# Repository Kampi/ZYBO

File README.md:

# ZYBO

## Table of Contents

- [ZYBO](#zybo)
  - [Table of Contents](#table-of-contents)
  - [About](#about)
  - [Examples](#examples)
  - [Projects](#projects)
  - [Pmod](#pmod)
  - [Maintainer](#maintainer)

## About

This repository contains several VHDL/C/Linux examples for [ZYNQ](https://www.xilinx.com/products/silicon-devices/soc/zynq-7000.html) devices from Xilinx which are designed for my [ZYBO](https://store.digilentinc.com/zybo-zynq-7000-arm-fpga-soc-trainer-board/).

Please visit my [blog](https://www.kampis-elektroecke.de/) when you need more information about the examples or about the projects.

## Examples

This directory contains the following examples from my ZYNQ tutorial:

| **Example** | **Description** |
|---|---|
| ProcessingSystem | Simple design to learn how to use the programmable logic and the [Processing System](https://www.xilinx.com/support/documentation/ip_documentation/processing_system7/v5_5/pg082-processing-system7.pdf) to read and write I/O by using the [AXI GPIO](https://www.xilinx.com/support/documentation/ip_documentation/axi_gpio/v2_0/pg144-axi-gpio.pdf). |
| Interrupts | Basic interrupt example to understand the ARM and programmable logic interrupt system. |
| XADC | Learn and understand how to use the integrated [XADC](https://www.xilinx.com/support/documentation/user_guides/ug480_7Series_XADC.pdf) to sample analog values. |
| FIFO | Small example how to use an [AXI-Stream FIFO](https://www.xilinx.com/support/documentation/ip_documentation/axi_fifo_mm_s/v4_1/pg080-axi-fifo-mm-s.pdf) in interrupt and polled mode. |
| ClockingWizard | Dynamic reconfiguration example for the [Clocking Wizard](https://www.xilinx.com/support/documentation/ip_documentation/clk_wiz/v6_0/pg065-clk-wiz.pdf). |

## Projects

This directory contains the following projects:

| **Project** | **Description** |
|---|---|
| DigitalAudio | A full I2S digital audio project for the FPGA and the Processing System based on [my tutorial](https://www.kampis-elektroecke.de/fpga/digitale-audioverarbeitung/). |
| DigitalVideo | A digital video processing project including VGA video output and OV7670 camera sensor input for the FPGA and the Processing System. |

## Pmod

This directory contains different Pmods for my ZYBO (designed with KiCad).

| **Pmod** | **Description** |
|---|---|
| LED | Simple 8-bit LED output. |
| OV7670 | Pmod adapter for the Arduino OV7670 camera module. |

## Maintainer

- [Daniel Kampert](mailto:DanielKampert@kampis-elektroecke.de)

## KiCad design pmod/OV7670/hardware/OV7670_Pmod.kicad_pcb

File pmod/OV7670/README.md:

# OV7670-Pmod

## Table of Contents

- [OV7670-Pmod](#ov7670-pmod)
  - [Table of Contents](#table-of-contents)
  - [About](#about)
  - [Pinout](#pinout)
  - [History](#history)
  - [Maintainer](#maintainer)

## About

OV7670-Pmod for for the ZYBO This PMod is used by the Camera Viewer project.

## Pinout

| **Signal**  | **X2**   | **X1**   |
|:-----------:|:--------:|:--------:|
| Reset       | -        | IO3      |
| PWDWN       | -        | IO4      |
| SIOC        | -        | IO7      |
| SIDO        | -        | IO8      |
| VSYNC       | -        | IO2      |
| PCLK        | -        | IO6      |
| HREF        | -        | IO1      |
| XCLK        | -        | IO5      |
| D0          | IO1      | -        |
| D1          | IO2      | -        |
| D2          | IO3      | -        |
| D3          | IO4      | -        |
| D4          | IO5      | -        |
| D5          | IO6      | -        |
| D6          | IO7      | -        |
| D7          | IO8      | -        |

## History

| **Version**  | **Description**                            | **Date**   |
|:------------:|:------------------------------------------:|:----------:|
| 1.2          | First release                     			| 18.04.2021 |

## Maintainer

- [Daniel Kampert](mailto:DanielKampert@kampis-elektroecke.de)

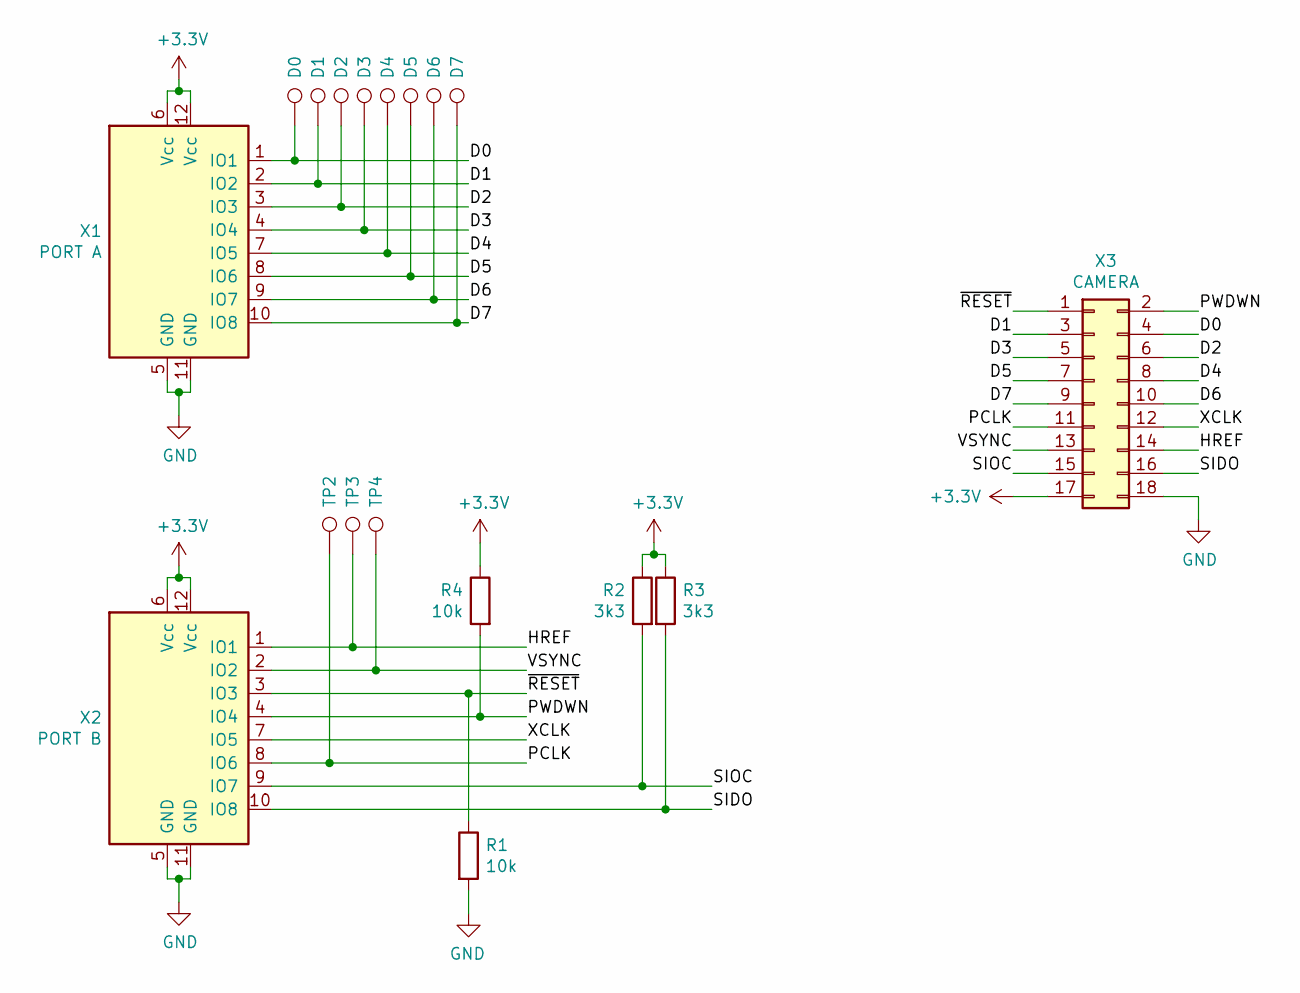
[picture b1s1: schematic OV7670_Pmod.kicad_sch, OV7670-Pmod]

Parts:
D0, D1, D2, D3, D4, D5, D6, D7: TestPoint_Pad_D1.0mm
R1, R4: 10k; R_0805_2012Metric_Pad1.15x1.40mm_HandSolder
R2, R3: 3k3; R_0805_2012Metric_Pad1.15x1.40mm_HandSolder
TP2: PCLK; TestPoint_Pad_D1.0mm
TP3: HREF; TestPoint_Pad_D1.0mm
TP4: VSYNC; TestPoint_Pad_D1.0mm
X1: PORT A; Pmod-Header-2x06
X2: PORT B; Pmod-Header-2x06
X3: CAMERA; PinSocket_2x09_P2.54mm_Horizontal

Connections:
+3V3: R2.1, R3.1, R4.1, X1.6 (Vcc), X1.12 (Vcc), X2.6 (Vcc), X2.12 (Vcc), X3.17
/D0: D0.1, X1.1 (IO1), X3.4
/D1: D1.1, X1.2 (IO2), X3.3
/D2: D2.1, X1.3 (IO3), X3.6
/D3: D3.1, X1.4 (IO4), X3.5
/D4: D4.1, X1.7 (IO5), X3.8
/D5: D5.1, X1.8 (IO6), X3.7
/D6: D6.1, X1.9 (IO7), X3.10
/D7: D7.1, X1.10 (IO8), X3.9
/HREF: TP3.1, X2.1 (IO1), X3.14
/PCLK: TP2.1, X2.8 (IO6), X3.11
/PWDWN: R4.2, X2.4 (IO4), X3.2
/SIDO: R3.2, X2.10 (IO8), X3.16
/SIOC: R2.2, X2.9 (IO7), X3.15
/VSYNC: TP4.1, X2.2 (IO2), X3.13
/XCLK: X2.7 (IO5), X3.12
/~RESET: R1.1, X2.3 (IO3), X3.1
GND: R1.2, X1.5 (GND), X1.11 (GND), X2.5 (GND), X2.11 (GND), X3.18

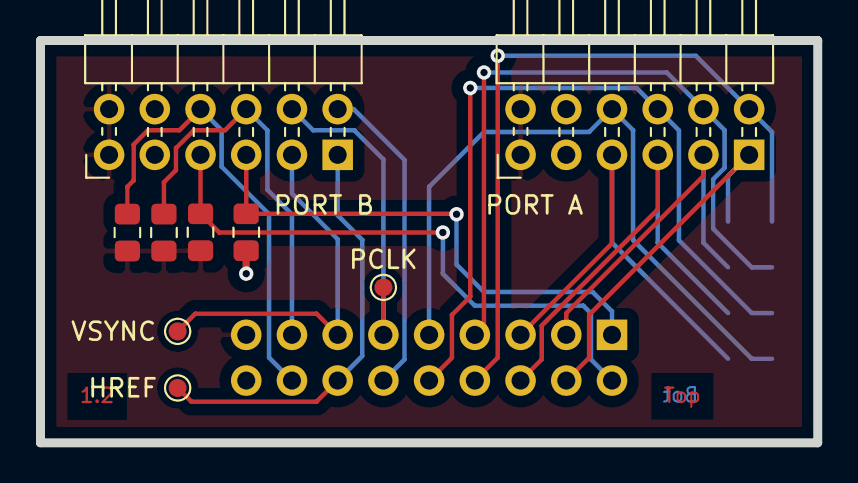
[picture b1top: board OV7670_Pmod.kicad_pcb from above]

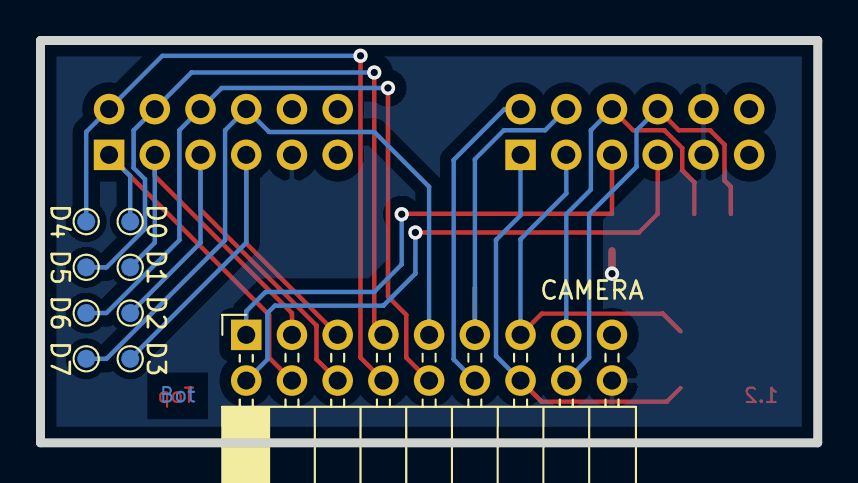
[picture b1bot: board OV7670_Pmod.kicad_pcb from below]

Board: 2 copper layers, 43.2 x 22.4 mm, 18 parts (9 on the bottom side), 18 nets.

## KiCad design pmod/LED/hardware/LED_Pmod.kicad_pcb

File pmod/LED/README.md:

# LED-Pmod

## Table of Contents

- [LED-Pmod](#led-pmod)
  - [Table of Contents](#table-of-contents)
  - [About](#about)
  - [Pinout](#pinout)
  - [History](#history)
  - [Maintainer](#maintainer)

## About

LED-Pmod for for the ZYBO.

## Pinout

| **LED**  | **X1**  |
|:--------:|:-------:|
| D0       | IO1     |
| D1       | IO2     |
| D2       | IO3     |
| D3       | IO4     |
| D4       | IO5     |
| D5       | IO6     |
| D6       | IO7     |
| D7       | IO8     |

## History

| **Version**  | **Description**                            | **Date**   |
|:------------:|:------------------------------------------:|:----------:|
| 1.0          | First release                              | 07.03.2021 |

## Maintainer

- [Daniel Kampert](mailto:DanielKampert@kampis-elektroecke.de)

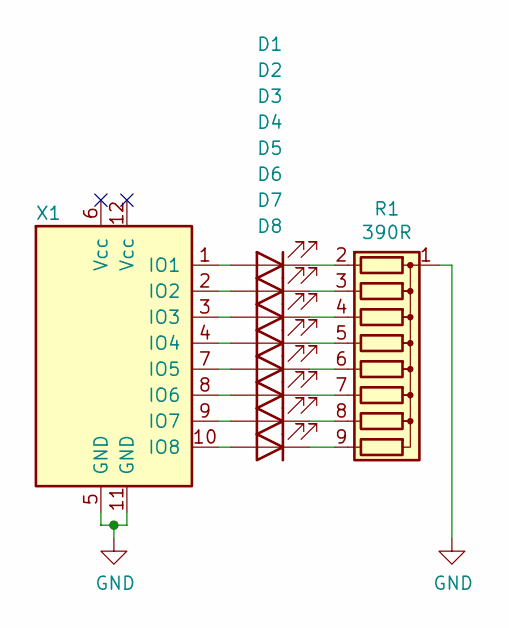
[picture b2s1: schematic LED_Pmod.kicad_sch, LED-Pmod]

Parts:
D1, D2, D3, D4, D5, D6, D7, D8: LED_D3.0mm
R1: 390R; R_Array_SIP9
X1: Pmod-Header-2x06

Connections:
GND: R1.1 (common), X1.5 (GND), X1.11 (GND)
unnamed: D1.1 (K), R1.2 (R1)
unnamed: D1.2 (A), X1.1 (IO1)
unnamed: D2.1 (K), R1.3 (R2)
unnamed: D2.2 (A), X1.2 (IO2)
unnamed: D3.1 (K), R1.4 (R3)
unnamed: D3.2 (A), X1.3 (IO3)
unnamed: D4.1 (K), R1.5 (R4)
unnamed: D4.2 (A), X1.4 (IO4)
unnamed: D5.1 (K), R1.6 (R5)
unnamed: D5.2 (A), X1.7 (IO5)
unnamed: D6.1 (K), R1.7 (R6)
unnamed: D6.2 (A), X1.8 (IO6)
unnamed: D7.1 (K), R1.8 (R7)
unnamed: D7.2 (A), X1.9 (IO7)
unnamed: D8.1 (K), R1.9 (R8)
unnamed: D8.2 (A), X1.10 (IO8)

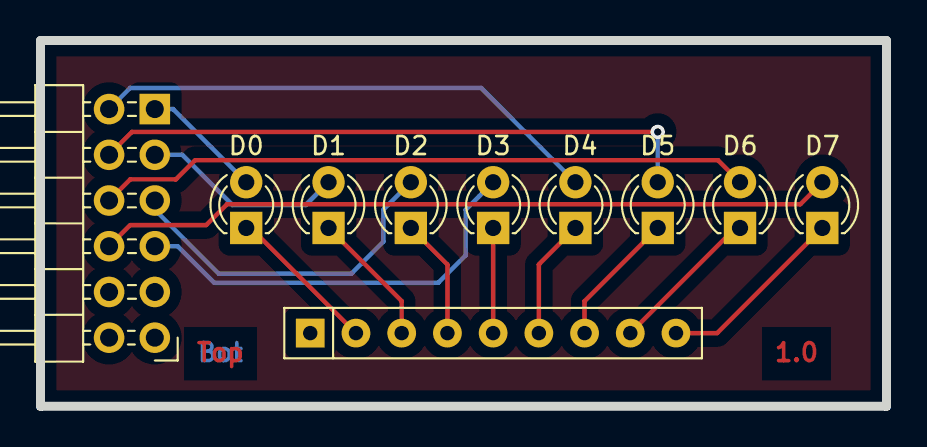
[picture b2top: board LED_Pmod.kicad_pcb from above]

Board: 2 copper layers, 47.0 x 20.3 mm, 10 parts (0 on the bottom side), 17 nets.

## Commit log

2021-06-04 Remove old files
2021-07-17 Add I2S receiver project, update projects to Vivado 2020.2, clean up projects
2021-07-17 Add documents
2021-07-17 Update nRF project to output MCLK
2021-07-23 Clean up
2021-07-24 Clean up, add first working version of the I2S receiver
2021-07-24 Add missing files
2021-07-25 AudioRecorder: - Add writer for .wav file format - Add writing from DMA to SD card
    AudioInspector:
    - Add file
    Misc:
    - Update README
    - Remove old files
2021-08-01 Add second nRF52 project for the audio player tutorial
2021-08-01 Clean up I2S receiver project
2022-12-11 Working on DigitalAudio project
2023-08-28 Add missing PMOD projects
2023-08-28 Add journal files to git ignore
2023-08-28 Remove useless examples
2023-08-28 Add documentation
2023-08-28 Fix typo
2023-08-28 Rework gitignore
2023-08-28 Fix typo in image path
2023-08-28 Change gitignore
2023-08-30 Add platform project for minimal linux example
